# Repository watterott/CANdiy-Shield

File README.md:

# CANdiy-Shield
The CANdiy-Shield is a plug-on module for Arduino with CAN-Bus (Controller Area Network) connectivity.

* Microchip CAN Controller (SPI)
* Microchip CAN Transceiver
* Switchable between 3V3 or 5V logic level (only CANdiy-Shield v2)
* 2 CAN connectors (RJ45)
* Prototyping Area
* Compatible with all Arduino Boards (SPI connection via 6-Pin ISP connector)
* Open-Source and released under the [Creative Commons Attribution Share-Alike License](https://creativecommons.org/licenses/by-sa/4.0/).
* **[Documentation on learn.watterott.com](https://learn.watterott.com)**

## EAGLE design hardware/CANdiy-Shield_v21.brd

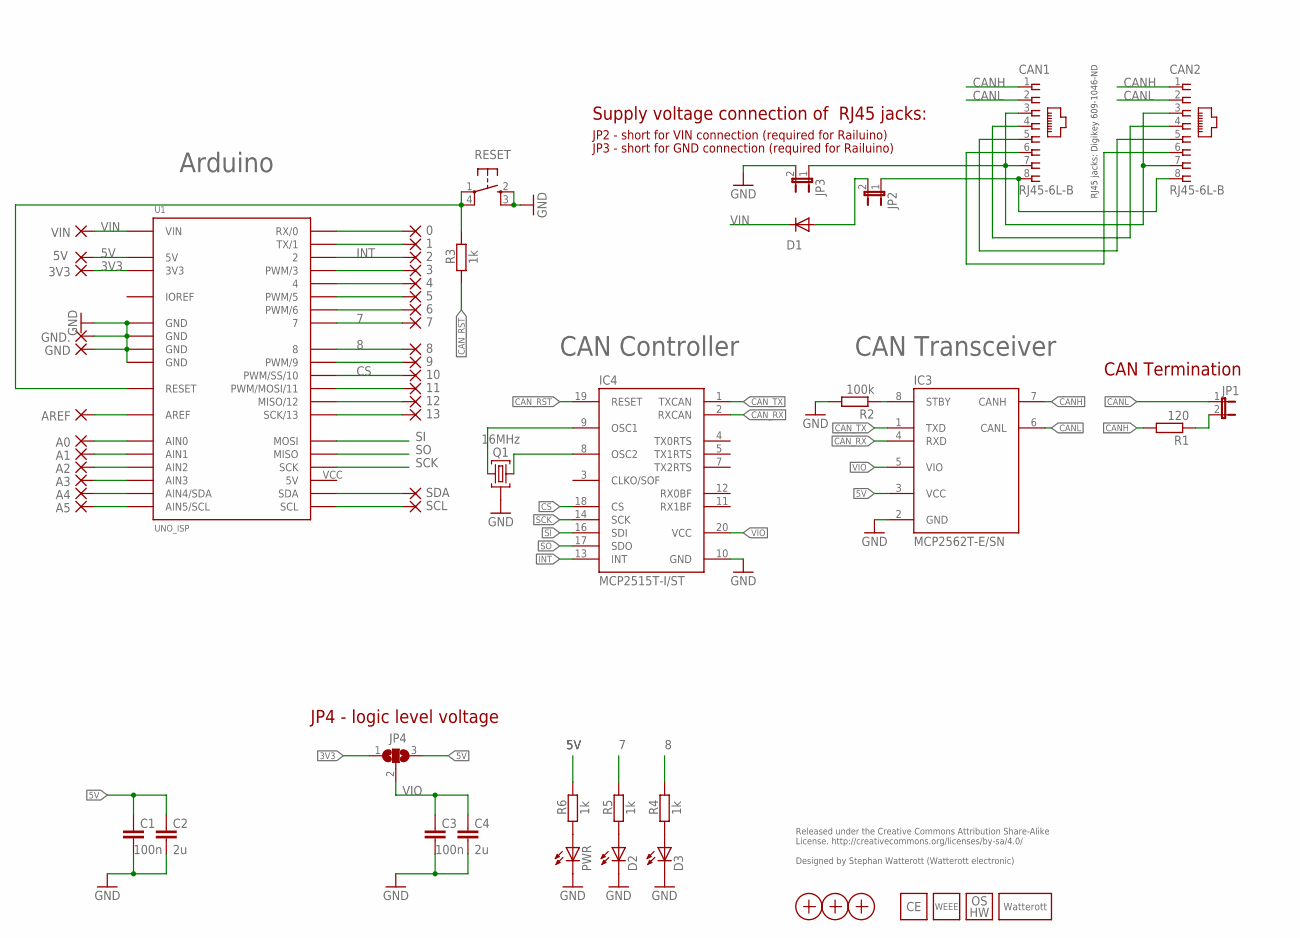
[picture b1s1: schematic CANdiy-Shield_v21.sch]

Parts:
0, 1, 2, 3, 3V3, 4, 5, 5V, 6, 7, 8, 9, 10, 11, 12, 13: 1,6/0,8
A0, A1, A2, A3, A4, A5: 1,6/0,8
AREF: 1,6/0,8
C1, C3: 100n; C0603
C2, C4: 2u; C0603
CAN1, CAN2: RJ45-6L-B; RJ45-NO-SHIELD
D1: CGRM4001-G; SOD-123_MINI-SMA
D2, D3: LEDCHIPLED_0603; CHIPLED_0603
GND, GND.: 1,6/0,8
IC3: MCP2562T-E/SN; SO08
IC4: MCP2515T-I/ST; TSSOP20
JP1, JP2, JP3: JP1E; JP1
JP4: SJ2W; SJ_2
LOGO3: LOGO-9; LOGO_9MM
LOGO4: LOGO_CE-2; CE_2MM
LOGO5: LOGO_OSHW-3; OSHW_3MM
LOGO6: LOGO_WEEE-4; WEEE_4MM
PWR: LEDCHIPLED_0603; CHIPLED_0603
Q1: 16MHz; CRYSTAL_32X13
R1: 120; R0603
R2: 100k; R0603
R3, R4, R5, R6: 1k; R0603
RESET: SW_SMDS; SW_SMD4
SCL: 1,6/0,8
SDA: 1,6/0,8
U1: UNO_ISP
VIN: 1,6/0,8
X1, X2, X3: PASSER-07; PASSER_07MM

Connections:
0: 0.1, U1.0 (RX/0)
1: 1.1, U1.1 (TX/1)
3: 3.1, U1.3 (PWM/3)
3V3: 3V3.1, JP4.1, U1.3V3
4: 4.1, U1.4
5: 5.1, U1.5 (PWM/5)
5V: 5V.1, C1.1, C2.1, IC3.3 (VCC), JP4.3, R6.1, U1.5V
6: 6.1, U1.6 (PWM/6)
7: 7.1, R5.1, U1.7
8: 8.1, R4.1, U1.8
9: 9.1, U1.9 (PWM/9)
11: 11.1, U1.11 (PWM/MOSI/11)
12: 12.1, U1.12 (MISO/12)
13: 13.1, U1.13 (SCK/13)
A0: A0.1, U1.AIN0
A1: A1.1, U1.AIN1
A2: A2.1, U1.AIN2
A3: A3.1, U1.AIN3
A4: A4.1, U1.AIN4 (AIN4/SDA)
A5: A5.1, U1.AIN5 (AIN5/SCL)
AREF: AREF.1, U1.AREF
CANH: CAN1.1, CAN2.1, IC3.7 (CANH), R1.2
CANL: CAN1.2, CAN2.2, IC3.6 (CANL), JP1.1
CAN_RST: IC4.19 (RESET), R3.2
CAN_RX: IC3.4 (RXD), IC4.2 (RXCAN)
CAN_TX: IC3.1 (TXD), IC4.1 (TXCAN)
CS: 10.1, IC4.18 (CS), U1.10 (PWM/SS/10)
GND: C1.2, C2.2, C3.2, C4.2, D2.C, D3.C, GND.1, GND..1, IC3.2 (GND), IC4.10 (GND), JP3.2, PWR.C, Q1.GND, R2.2, RESET.2 (S), RESET.3 (S1), U1.GND@1 (GND), U1.GND@2 (GND), U1.GND@3 (GND), U1.GND@4 (GND)
INT: 2.1, IC4.13 (INT), U1.2
IOREF: U1.IOREF
unnamed: CAN1.8, CAN2.8, JP2.1
unnamed: IC3.8 (STBY), R2.1
unnamed: CAN1.3, CAN1.7, CAN2.3, CAN2.7, JP3.1
unnamed: JP1.2, R1.1
unnamed: SCL.1, U1.SCL
unnamed: SDA.1, U1.SDA
unnamed: D3.A, R4.2
unnamed: PWR.A, R6.2
unnamed: D2.A, R5.2
unnamed: D1.A, JP2.2
unnamed: CAN1.4, CAN2.4
unnamed: CAN1.5, CAN2.5
unnamed: CAN1.6, CAN2.6
OSC1: IC4.9 (OSC1), Q1.2
OSC2: IC4.8 (OSC2), Q1.1
RESET: R3.1, RESET.1, RESET.4 (P1), U1.RST (RESET)
SCK: IC4.14 (SCK), U1.SCK
SI: IC4.16 (SDI), U1.MOSI
SO: IC4.17 (SDO), U1.MISO
VIN: D1.C, U1.VIN, VIN.1
VIO: C3.1, C4.1, IC3.5 (VIO), IC4.20 (VCC), JP4.2

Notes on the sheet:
Released under the Creative Commons Attribution Share-Alike License. http://creativecommons.org/licenses/by-sa/4.0/ Designed by Stephan Watterott (Watterott electronic)
Arduino
CAN Termination
Supply voltage connection of RJ45 jacks:
JP3 - short for GND connection (required for Railuino)
JP2 - short for VIN connection (required for Railuino)
RJ45 jacks: Digikey 609-1046-ND
CAN Controller
CAN Transceiver
JP4 - logic level voltage

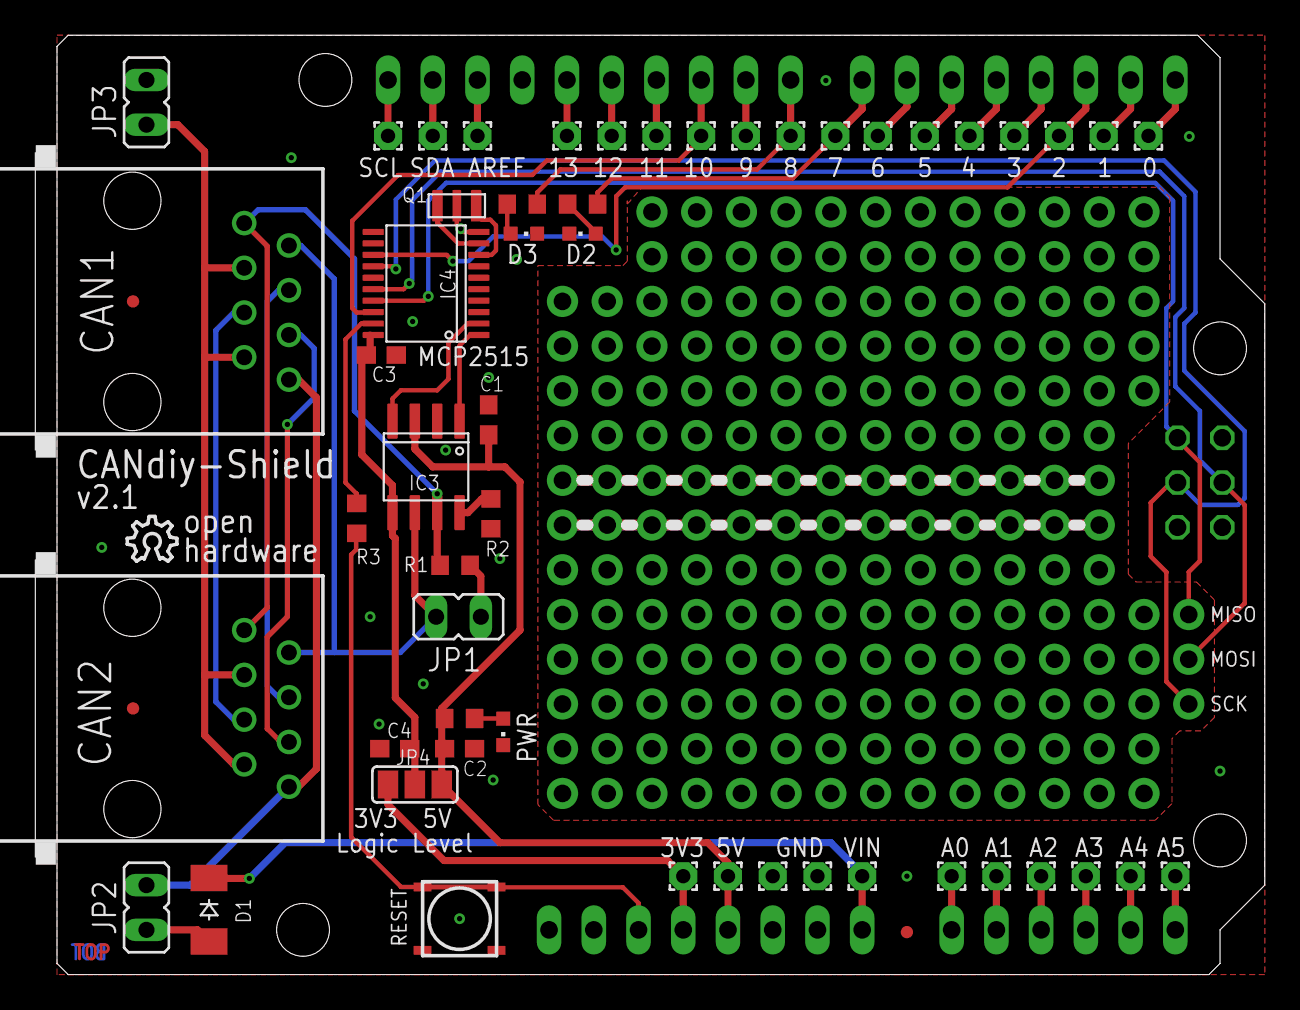
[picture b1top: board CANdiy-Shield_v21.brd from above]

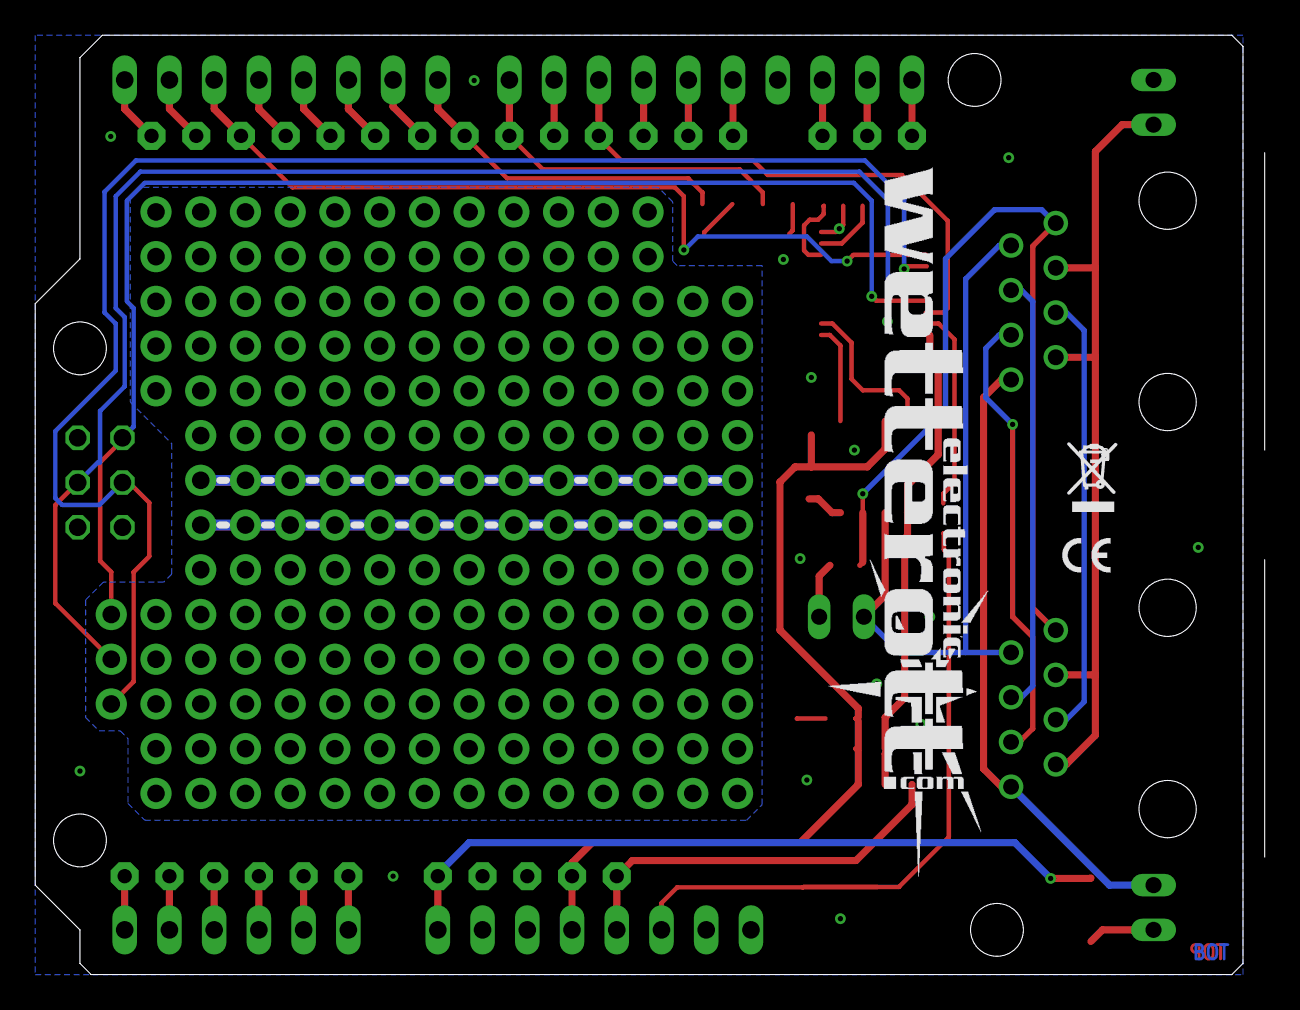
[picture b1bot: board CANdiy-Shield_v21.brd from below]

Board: 2 copper layers, 69.8 x 53.3 mm, 60 parts (3 on the bottom side), 50 nets.

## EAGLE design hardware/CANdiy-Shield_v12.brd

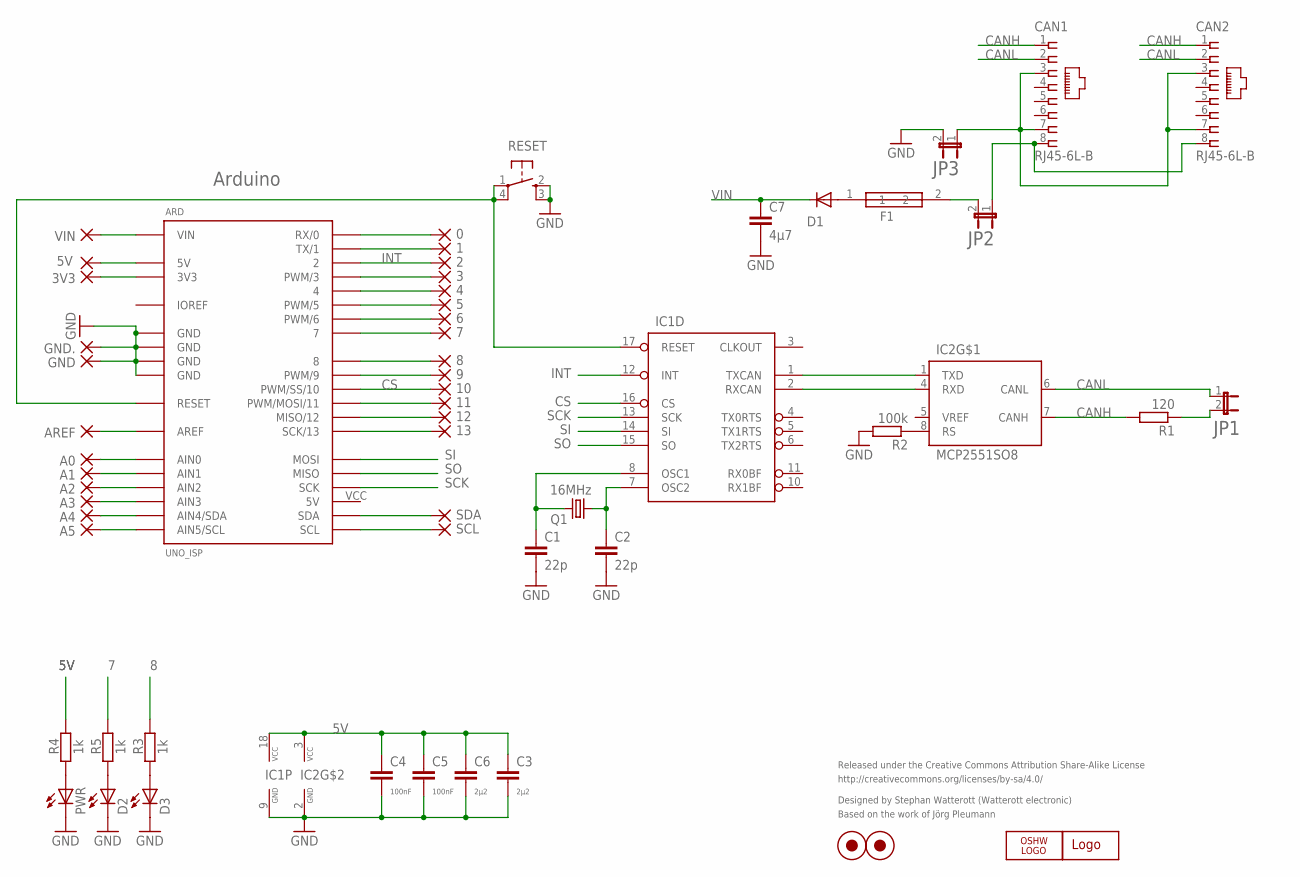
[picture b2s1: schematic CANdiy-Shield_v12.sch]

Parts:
0, 1, 2, 3, 3V3, 4, 5, 5V, 6, 7, 8, 9, 10, 11, 12, 13: 1,6/0,8
A0, A1, A2, A3, A4, A5: 1,6/0,8
ARD: UNO_ISP
AREF: 1,6/0,8
C1, C2: 22p; C0603
C3, C6: 2µ2; C0603
C4, C5: 100nF; C0603
C7: 4µ7; C1206
CAN1, CAN2: RJ45-6L-B; RJ45-NO-SHIELD
D1: CGRM4001-G; SOD-123_MINI-SMA
D2, D3: LEDCHIPLED_0603; CHIPLED_0603
F1: F1; L1812
GND, GND.: 1,6/0,8
IC1: MCP2515SO; SO-18W
IC2: MCP2551SO8; SO08
JP1, JP2, JP3: JP1E; JP1
LOGO2: OSHW_LOGO_6MILX0100-NT; OSHW_6X100_NOTEXT
PWR: LEDCHIPLED_0603; CHIPLED_0603
Q1: 16MHz; HC49UP
R1: 120; R0603
R2: 100k; R0603
R3, R4, R5: 1k; R0603
RESET: SW_SMDS; SW_SMD4
SCL: 1,6/0,8
SDA: 1,6/0,8
U$1: WE-LOGO
VIN: 1,6/0,8
X_1, X_2: PASS_1MM; ROUND_1MM

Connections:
3V3: 3V3.1, ARD.3V3
5V: 5V.1, ARD.5V, C3.1, C4.1, C5.1, C6.1, IC1.18 (VCC), IC2.3 (VCC), R4.1
7: 7.1, ARD.7, R5.1
8: 8.1, ARD.8, R3.1
9: 9.1, ARD.9 (PWM/9)
A0: A0.1, ARD.AIN0
AERF: ARD.AREF, AREF.1
CANH: CAN1.1, CAN2.1, IC2.7 (CANH), R1.2
CANL: CAN1.2, CAN2.2, IC2.6 (CANL), JP1.1
CS: 10.1, ARD.10 (PWM/SS/10), IC1.16 (CS)
GND: ARD.GND@1 (GND), ARD.GND@2 (GND), ARD.GND@3 (GND), ARD.GND@4 (GND), C1.2, C2.2, C3.2, C4.2, C5.2, C6.2, C7.2, D2.C, D3.C, GND.1, GND..1, IC1.9 (GND), IC2.2 (GND), JP3.2, PWR.C, R2.2, RESET.2 (S), RESET.3 (S1)
INT: 2.1, ARD.2, IC1.12 (INT)
IOREF: ARD.IOREF
unnamed: C2.1, IC1.7 (OSC2), Q1.1
unnamed: C1.1, IC1.8 (OSC1), Q1.2
unnamed: CAN1.8, CAN2.8, JP2.1
unnamed: IC2.8 (RS), R2.1
unnamed: CAN1.3, CAN1.7, CAN2.3, CAN2.7, JP3.1
unnamed: JP1.2, R1.1
unnamed: ARD.SCL, SCL.1
unnamed: ARD.SDA, SDA.1
unnamed: D3.A, R3.2
unnamed: PWR.A, R4.2
unnamed: D2.A, R5.2
unnamed: 11.1, ARD.11 (PWM/MOSI/11)
unnamed: 12.1, ARD.12 (MISO/12)
unnamed: 13.1, ARD.13 (SCK/13)
unnamed: 6.1, ARD.6 (PWM/6)
unnamed: 5.1, ARD.5 (PWM/5)
unnamed: 4.1, ARD.4
unnamed: 3.1, ARD.3 (PWM/3)
unnamed: 1.1, ARD.1 (TX/1)
unnamed: 0.1, ARD.0 (RX/0)
unnamed: A1.1, ARD.AIN1
unnamed: A2.1, ARD.AIN2
unnamed: A3.1, ARD.AIN3
unnamed: A4.1, ARD.AIN4 (AIN4/SDA)
unnamed: A5.1, ARD.AIN5 (AIN5/SCL)
unnamed: D1.A, F1.1
unnamed: F1.2, JP2.2
RESET: ARD.RST (RESET), IC1.17 (RESET), RESET.1, RESET.4 (P1)
RXCAN: IC1.2 (RXCAN), IC2.4 (RXD)
SCK: ARD.SCK, IC1.13 (SCK)
SI: ARD.MOSI, IC1.14 (SI)
SO: ARD.MISO, IC1.15 (SO)
TXCAN: IC1.1 (TXCAN), IC2.1 (TXD)
VIN: ARD.VIN, C7.1, D1.C, VIN.1

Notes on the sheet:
Released under the Creative Commons Attribution Share-Alike License
http://creativecommons.org/licenses/by-sa/4.0/
Designed by Stephan Watterott (Watterott electronic)
Arduino
Based on the work of Jörg Pleumann

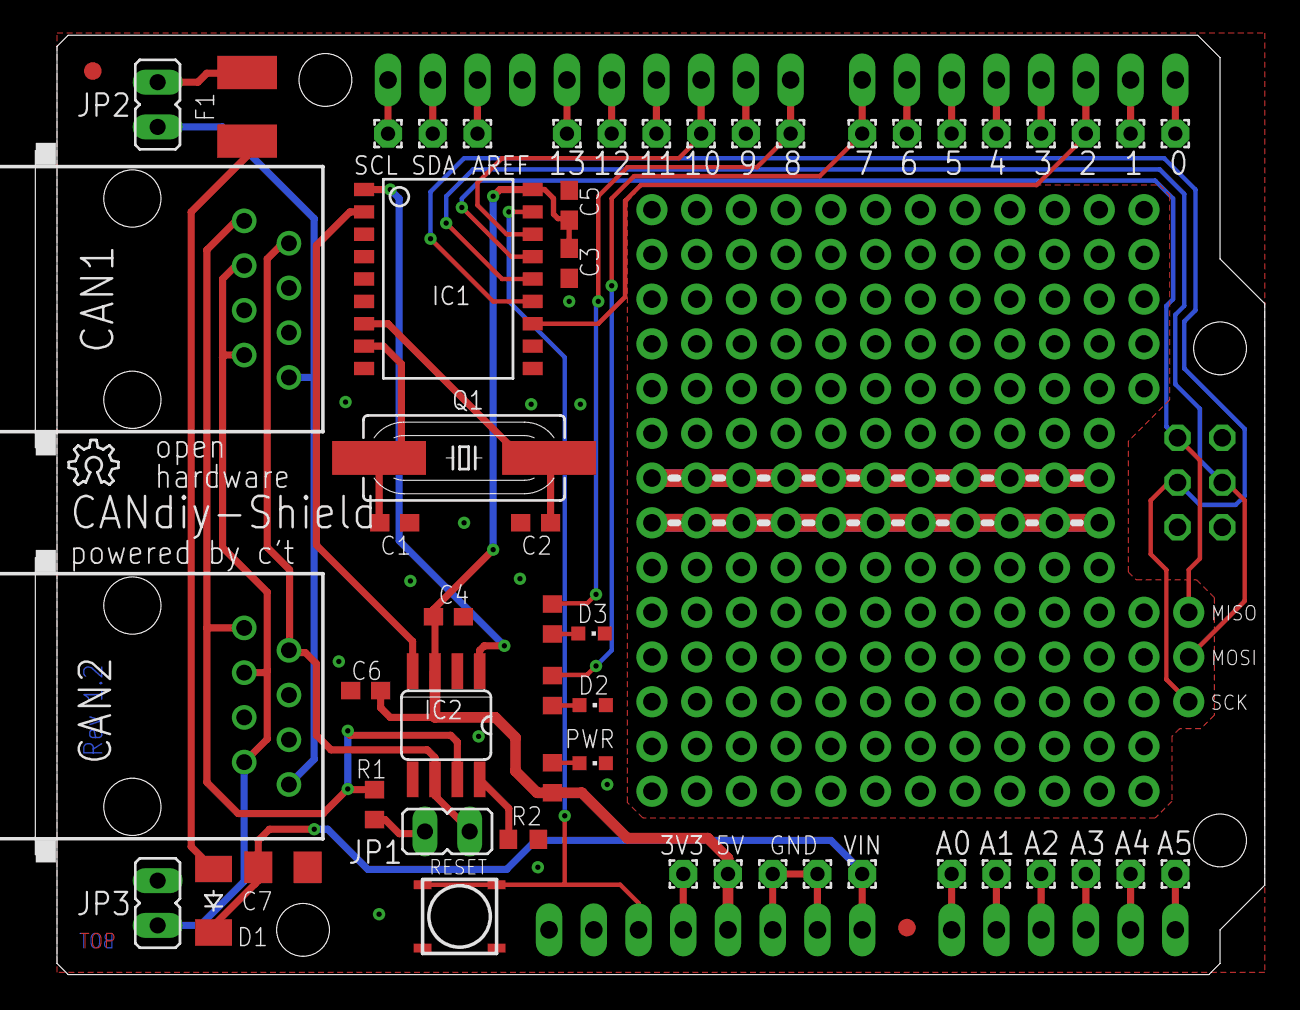
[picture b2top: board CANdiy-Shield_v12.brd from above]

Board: 2 copper layers, 69.8 x 53.3 mm, 59 parts (1 on the bottom side), 46 nets.

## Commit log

2018-11-23 added CANdiy-FD v1.1
2019-06-03 updated schematics
2019-11-21 added rev 2.1
2019-11-21 updated pdf
